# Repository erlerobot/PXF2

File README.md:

#The PixHawk Fire Cape 2.0 (PXF 2.0)

The PixHawk Fire Cape 2.0 (PXF 2.0) is an open hardware multi-platform shield for making drones using the APM autopilot supported by the Dronecode Foundation. This board is the evolution of the PXF, a project initiated by Philip Rowse to create an open hardware daughter board for Linux-based autopilots.

The shield is compatible with the following boards:

- BeagleBone Black
- Raspberry Pi
- Raspberry Pi 2
- Banana Pi
- Orange Pi
- Odroid-C1
- Odroid-C1+

(Note: not all these boards have been tested experimentally but the shield offers compatibility with the corresponding headers)

### Acquire the board
THIS SHIELD IS NOT SOLD INDIVIDUALLY. COMMERCIAL SOLUTIONS BASED ON THE PIXHAWK FIRE CAPE 2.0 ARE LISTED BELOW:
- [Erle-Brain 2.0](http://erlerobotics.com/blog/product/erle-brain-v2/)

If you'd like to be listed here contact victor@erlerobotics.com.

### Acknowledgements
This work has been enabled by Philip Rowse, Andrew Tridgell, Siddarth Purohit and all the contributors and supporters of the BeaglePilot, APM, and PX4 projects. Special mention to the DIYDrones community.

### License
GPLv3

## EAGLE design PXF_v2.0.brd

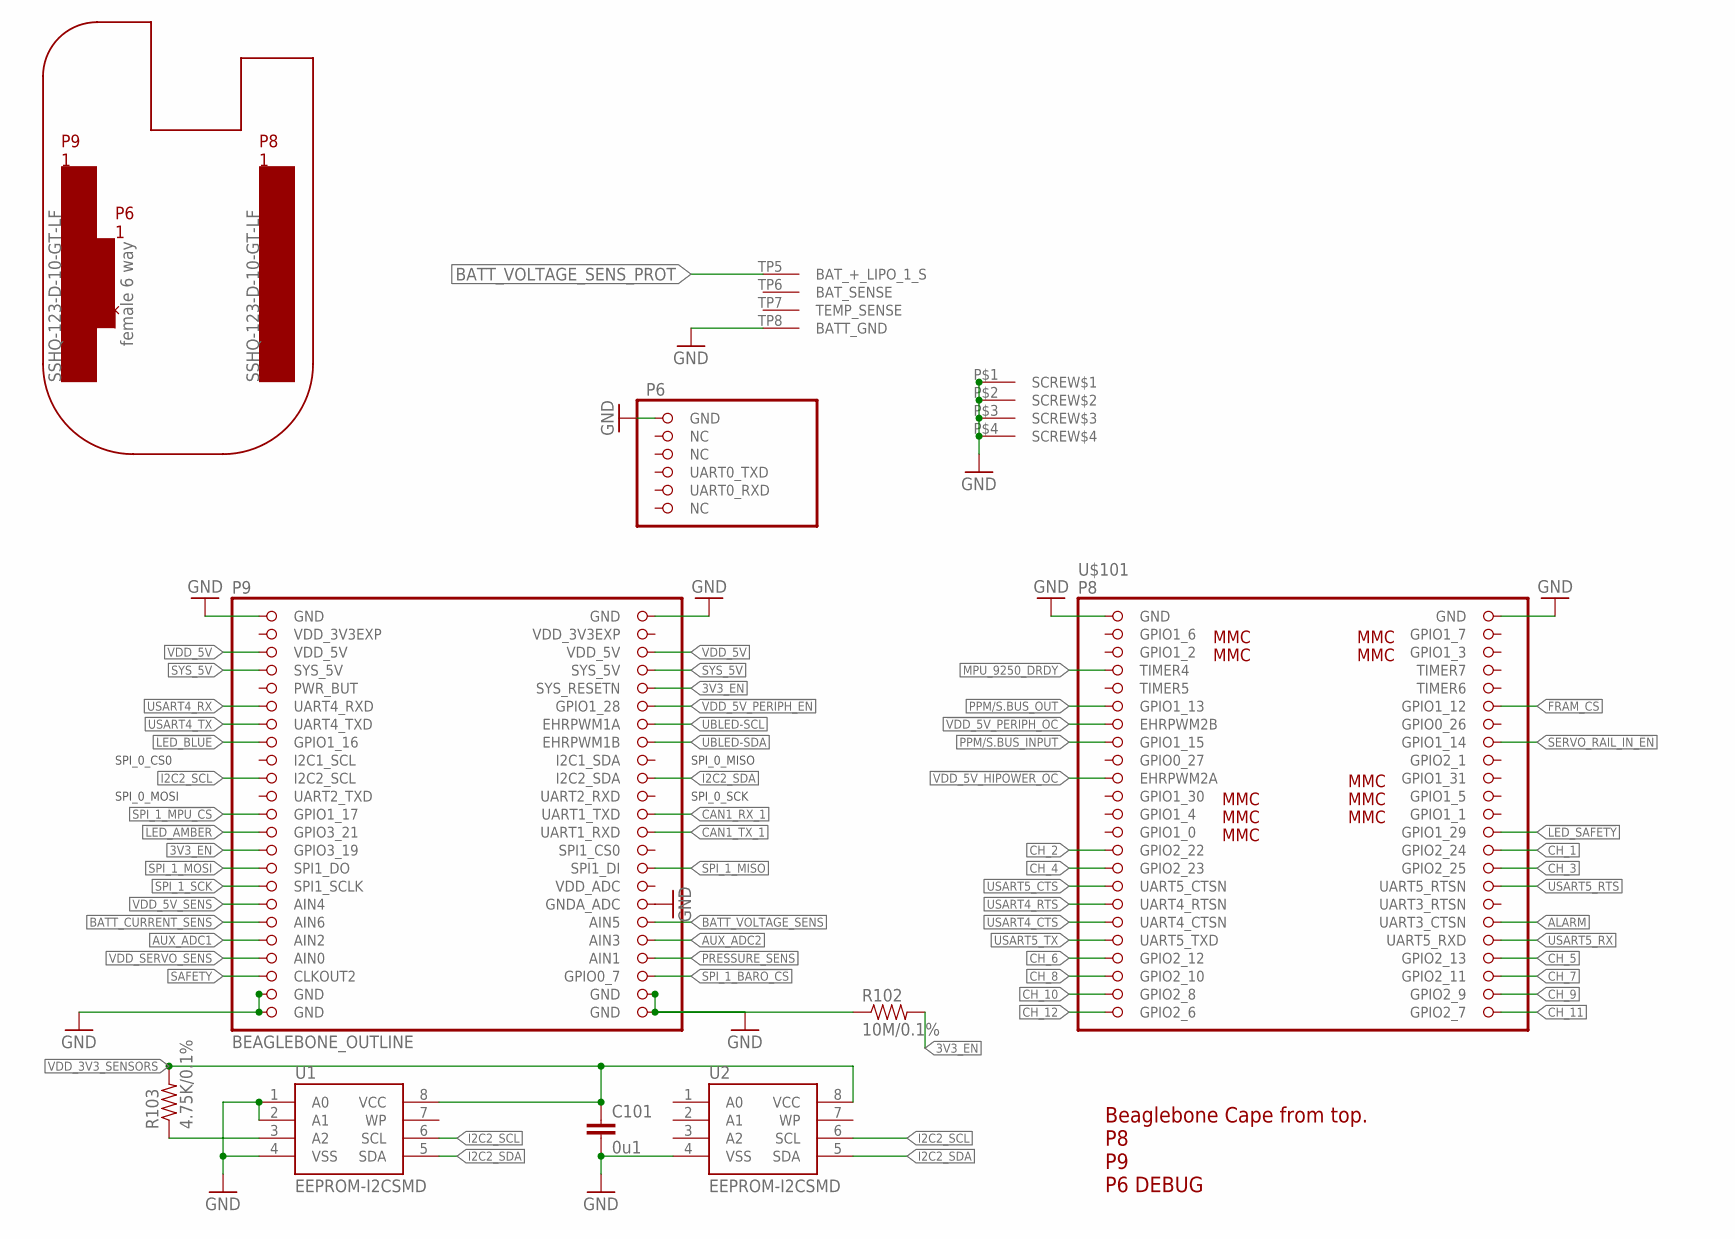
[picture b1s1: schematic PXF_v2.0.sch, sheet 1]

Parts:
C101: 0u1; 0402-CAP; PARTNO CC0402ZRY5V7BB104
R102: 10M/0.1%; 0402-RES; PARTNO RC0402FR-0710ML
R103: 4.75K/0.1%; 0402-RES; PARTNO RC0402FR-074K75L
U1: EEPROM-I2CSMD; SO08; PARTNO AT24CS32-SSHM
U2: EEPROM-I2CSMD; SO08; PARTNO ATSHA204-SH-DA-TTR-ND
U$101: BEAGLEBONE_OUTLINE; BEAGLEBONE_SHIELD

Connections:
3V3_EN: R102.P$2 (2), U$101.56 (SYS_RESETN), U$101.73 (GPIO3_19); also elsewhere on the board
!FRAM_CS: U$101.12 (GPIO1_12); also elsewhere on the board
!LED_AMBER: U$101.71 (GPIO3_21); also elsewhere on the board
!LED_BLUE: U$101.61 (GPIO1_16); also elsewhere on the board
!LED_SAFETY: U$101.26 (GPIO1_29); also elsewhere on the board
!VDD_5V_HIPOWER_OC: U$101.19 (EHRPWM2A); also elsewhere on the board
!VDD_5V_PERIPH_EN: U$101.58 (GPIO1_28); also elsewhere on the board
!VDD_5V_PERIPH_OC: U$101.13 (EHRPWM2B); also elsewhere on the board
ALARM: U$101.36 (UART3_CTSN); also elsewhere on the board
AUX_ADC1: U$101.83 (AIN2); also elsewhere on the board
AUX_ADC2: U$101.84 (AIN3); also elsewhere on the board
BATT_CURRENT_SENS: U$101.81 (AIN6); also elsewhere on the board
BATT_VOLTAGE_SENS: U$101.82 (AIN5); also elsewhere on the board
BATT_VOLTAGE_SENS_PROT: U$101.TP5 (BAT_+_LIPO_1_S); also elsewhere on the board
CAN1_RX_1: U$101.70 (UART1_TXD); also elsewhere on the board
CAN1_TX_1: U$101.72 (UART1_RXD); also elsewhere on the board
CH_1: U$101.28 (GPIO2_24); also elsewhere on the board
CH_2: U$101.27 (GPIO2_22); also elsewhere on the board
CH_3: U$101.30 (GPIO2_25); also elsewhere on the board
CH_4: U$101.29 (GPIO2_23); also elsewhere on the board
CH_5: U$101.40 (GPIO2_13); also elsewhere on the board
CH_6: U$101.39 (GPIO2_12); also elsewhere on the board
CH_7: U$101.42 (GPIO2_11); also elsewhere on the board
CH_8: U$101.41 (GPIO2_10); also elsewhere on the board
CH_9: U$101.44 (GPIO2_9); also elsewhere on the board
CH_10: U$101.43 (GPIO2_8); also elsewhere on the board
CH_11: U$101.46 (GPIO2_7); also elsewhere on the board
CH_12: U$101.45 (GPIO2_6); also elsewhere on the board
GND: C101.P$2 (2), R102.P$1 (1), U1.1 (A0), U1.2 (A1), U1.4 (VSS), U2.4 (VSS), U$101.1 (GND), U$101.2 (GND), U$101.47 (GND), U$101.48 (GND), U$101.80 (GNDA_ADC), U$101.89 (GND), U$101.90 (GND), U$101.91 (GND), U$101.92 (GND), U$101.93 (GND), U$101.P$1 (SCREW$1), U$101.P$2 (SCREW$2), U$101.P$3 (SCREW$3), U$101.P$4 (SCREW$4), U$101.TP8 (BATT_GND); also elsewhere on the board
I2C2_SCL: U1.6 (SCL), U2.6 (SCL), U$101.65 (I2C2_SCL); also elsewhere on the board
I2C2_SDA: U1.5 (SDA), U2.5 (SDA), U$101.66 (I2C2_SDA); also elsewhere on the board
MPU_9250_DRDY: U$101.7 (TIMER4); also elsewhere on the board
unnamed: R103.P$1 (1), U1.3 (A2)
PPM/S.BUS_INPUT: U$101.15 (GPIO1_15); also elsewhere on the board
PPM/S.BUS_OUT: U$101.11 (GPIO1_13); also elsewhere on the board
PRESSURE_SENS: U$101.86 (AIN1); also elsewhere on the board
SAFETY: U$101.87 (CLKOUT2); also elsewhere on the board
SERVO_RAIL_IN_!EN: U$101.16 (GPIO1_14)
SPI_1_!BARO_CS: U$101.88 (GPIO0_7); also elsewhere on the board
SPI_1_!MPU_CS: U$101.69 (GPIO1_17); also elsewhere on the board
SPI_1_MISO: U$101.76 (SPI1_DI); also elsewhere on the board
SPI_1_MOSI: U$101.75 (SPI1_DO); also elsewhere on the board
SPI_1_SCK: U$101.77 (SPI1_SCLK); also elsewhere on the board
SYS_5V: U$101.53 (SYS_5V), U$101.54 (SYS_5V); also elsewhere on the board
UBLED-SCL: U$101.60 (EHRPWM1A); also elsewhere on the board
UBLED-SDA: U$101.62 (EHRPWM1B); also elsewhere on the board
USART4_CTS: U$101.35 (UART4_CTSN); also elsewhere on the board
USART4_RTS: U$101.33 (UART4_RTSN); also elsewhere on the board
USART4_RX: U$101.57 (UART4_RXD); also elsewhere on the board
USART4_TX: U$101.59 (UART4_TXD); also elsewhere on the board
USART5_CTS: U$101.31 (UART5_CTSN); also elsewhere on the board
USART5_RTS: U$101.32 (UART5_RTSN); also elsewhere on the board
USART5_RX: U$101.38 (UART5_RXD); also elsewhere on the board
USART5_TX: U$101.37 (UART5_TXD); also elsewhere on the board
VDD_3V3EXP: U$101.49 (VDD_3V3EXP), U$101.50 (VDD_3V3EXP)
VDD_3V3_SENSORS: C101.P$1 (1), R103.P$2 (2), U1.8 (VCC), U2.8 (VCC); also elsewhere on the board
VDD_5V: U$101.51 (VDD_5V), U$101.52 (VDD_5V); also elsewhere on the board
VDD_5V_SENS: U$101.79 (AIN4); also elsewhere on the board
VDD_SERVO_SENS: U$101.85 (AIN0); also elsewhere on the board

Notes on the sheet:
Beaglebone Cape from top. P8 P9 P6 DEBUG
SPI_0_CS0
SPI_0_MOSI
SPI_0_MISO
SPI_0_SCK

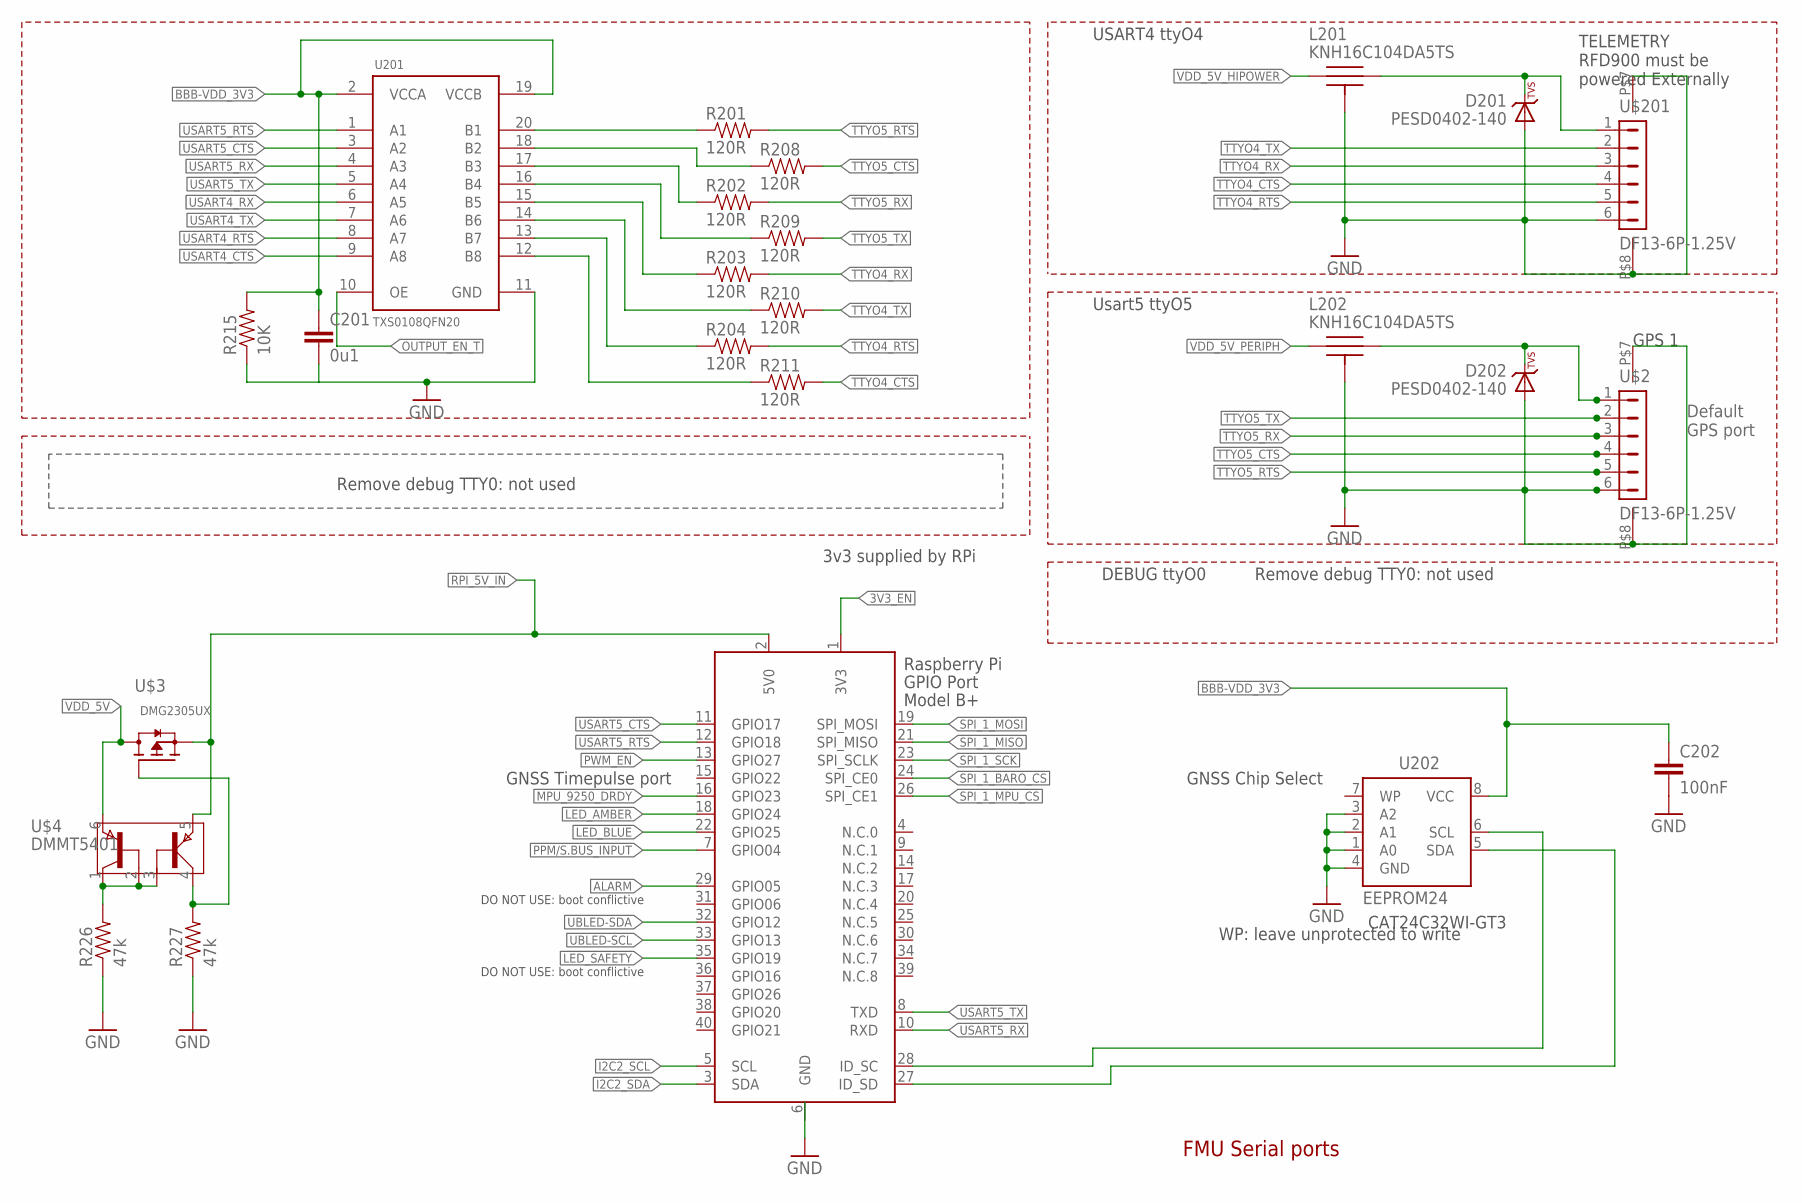
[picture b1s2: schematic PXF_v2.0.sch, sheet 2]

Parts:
C201: 0u1; 0402-CAP; PARTNO CC0402ZRY5V7BB104
C202: 100nF; 0402-CAP; PARTNO CC0402ZRY5V7BB104
D201, D202: PESD0402-140; 0402-TVS; PARTNO PESD0402-140
L201, L202: KNH16C104DA5TS; KYOCERA-KNH16-DA; PARTNO KNH16C104DA5TS
R201, R202, R203, R204, R208, R209, R210, R211: 120R; 0402-RES; PARTNO RC0402FR-07120RL
R215: 10K; 0402-RES; PARTNO ERA-2AEB103X
R226, R227: 47k; 0402-RES; PARTNO RC0402FR-07120RL
U201: TXS0108QFN20; QFN20-RGY; PARTNO TXS0108ERGYR
U202: EEPROM24; SOIC8
U$2, U$201: DF13-6P-1.25V; DF13C-6P-1.25V; PARTNO DF13C-6P-1.25V(20)
U$3: P-MOSFET; SOT23
U$4: DMMT5401; SOT26
X2: RASPI_BOARD_B+_F; RASPI_BOARD_B+_FULL

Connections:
3V3_EN: X2.1 (3V3); also elsewhere on the board
!LED_AMBER: X2.18 (GPIO24); also elsewhere on the board
!LED_BLUE: X2.22 (GPIO25); also elsewhere on the board
!LED_SAFETY: X2.35 (GPIO19); also elsewhere on the board
ALARM: X2.29 (GPIO05); also elsewhere on the board
BBB-VDD_3V3: C201.P$1 (1), C202.P$1 (1), R215.P$2 (2), U201.2 (VCCA), U201.19 (VCCB), U202.8 (VCC); also elsewhere on the board
GND: C201.P$2 (2), C202.P$2 (2), D201.A, D202.A, L201.P$3, L201.P$4, L201.P$5, L202.P$3, L202.P$4, L202.P$5, R215.P$1 (1), R226.P$1 (1), R227.P$1 (1), U201.11 (GND), U202.1 (A0), U202.2 (A1), U202.3 (A2), U202.4 (GND), U$2.6, U$2.P$7, U$2.P$8, U$201.6, U$201.P$7, U$201.P$8, X2.6 (GND); also elsewhere on the board
I2C2_SCL: X2.5 (SCL); also elsewhere on the board
I2C2_SDA: X2.3 (SDA); also elsewhere on the board
MPU_9250_DRDY: X2.16 (GPIO23); also elsewhere on the board
unnamed: U202.6 (SCL), X2.28 (ID_SC)
unnamed: U202.5 (SDA), X2.27 (ID_SD)
unnamed: D201.C, L201.P$2, U$201.1
unnamed: R226.P$2 (2), U$4.1, U$4.2, U$4.3
unnamed: R227.P$2 (2), U$3.G, U$4.4
unnamed: R208.P$1 (1), U201.18 (B2)
unnamed: R201.P$1 (1), U201.20 (B1)
unnamed: R202.P$1 (1), U201.17 (B3)
unnamed: R209.P$1 (1), U201.16 (B4)
unnamed: R203.P$1 (1), U201.15 (B5)
unnamed: R210.P$1 (1), U201.14 (B6)
unnamed: R204.P$1 (1), U201.13 (B7)
unnamed: R211.P$1 (1), U201.12 (B8)
unnamed: D202.C, L202.P$2, U$2.1
OUTPUT_EN_T: U201.10 (OE); also elsewhere on the board
PPM/S.BUS_INPUT: X2.7 (GPIO04); also elsewhere on the board
PWM_EN: X2.13 (GPIO27); also elsewhere on the board
RPI_5V_IN: U$3.S, U$4.5, X2.2 (5V0); also elsewhere on the board
SPI_1_!BARO_CS: X2.24 (SPI_CE0); also elsewhere on the board
SPI_1_!MPU_CS: X2.26 (SPI_CE1); also elsewhere on the board
SPI_1_MISO: X2.21 (SPI_MISO); also elsewhere on the board
SPI_1_MOSI: X2.19 (SPI_MOSI); also elsewhere on the board
SPI_1_SCK: X2.23 (SPI_SCLK); also elsewhere on the board
TTYO4_CTS: R211.P$2 (2), U$201.4
TTYO4_RTS: R204.P$2 (2), U$201.5
TTYO4_RX: R203.P$2 (2), U$201.3; also elsewhere on the board
TTYO4_TX: R210.P$2 (2), U$201.2; also elsewhere on the board
TTYO5_CTS: R208.P$2 (2), U$2.4
TTYO5_RTS: R201.P$2 (2), U$2.5
TTYO5_RX: R202.P$2 (2), U$2.3; also elsewhere on the board
TTYO5_TX: R209.P$2 (2), U$2.2; also elsewhere on the board
UBLED-SCL: X2.33 (GPIO13); also elsewhere on the board
UBLED-SDA: X2.32 (GPIO12); also elsewhere on the board
USART4_CTS: U201.9 (A8); also elsewhere on the board
USART4_RTS: U201.8 (A7); also elsewhere on the board
USART4_RX: U201.6 (A5); also elsewhere on the board
USART4_TX: U201.7 (A6); also elsewhere on the board
USART5_CTS: U201.3 (A2), X2.11 (GPIO17); also elsewhere on the board
USART5_RTS: U201.1 (A1), X2.12 (GPIO18); also elsewhere on the board
USART5_RX: U201.4 (A3), X2.10 (RXD); also elsewhere on the board
USART5_TX: U201.5 (A4), X2.8 (TXD); also elsewhere on the board
VDD_5V: U$3.D, U$4.6; also elsewhere on the board
VDD_5V_HIPOWER: L201.P$1; also elsewhere on the board
VDD_5V_PERIPH: L202.P$1; also elsewhere on the board

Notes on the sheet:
FMU Serial ports
Usart5 ttyO5
USART4 ttyO4
DEBUG ttyO0
Default GPS port
TELEMETRY RFD900 must be powered Externally
GPS 1
Remove debug TTY0: not used
CAT24C32WI-GT3
3v3 supplied by RPi
GNSS Timepulse port
GNSS Chip Select
DO NOT USE: boot conflictive
WP: leave unprotected to write

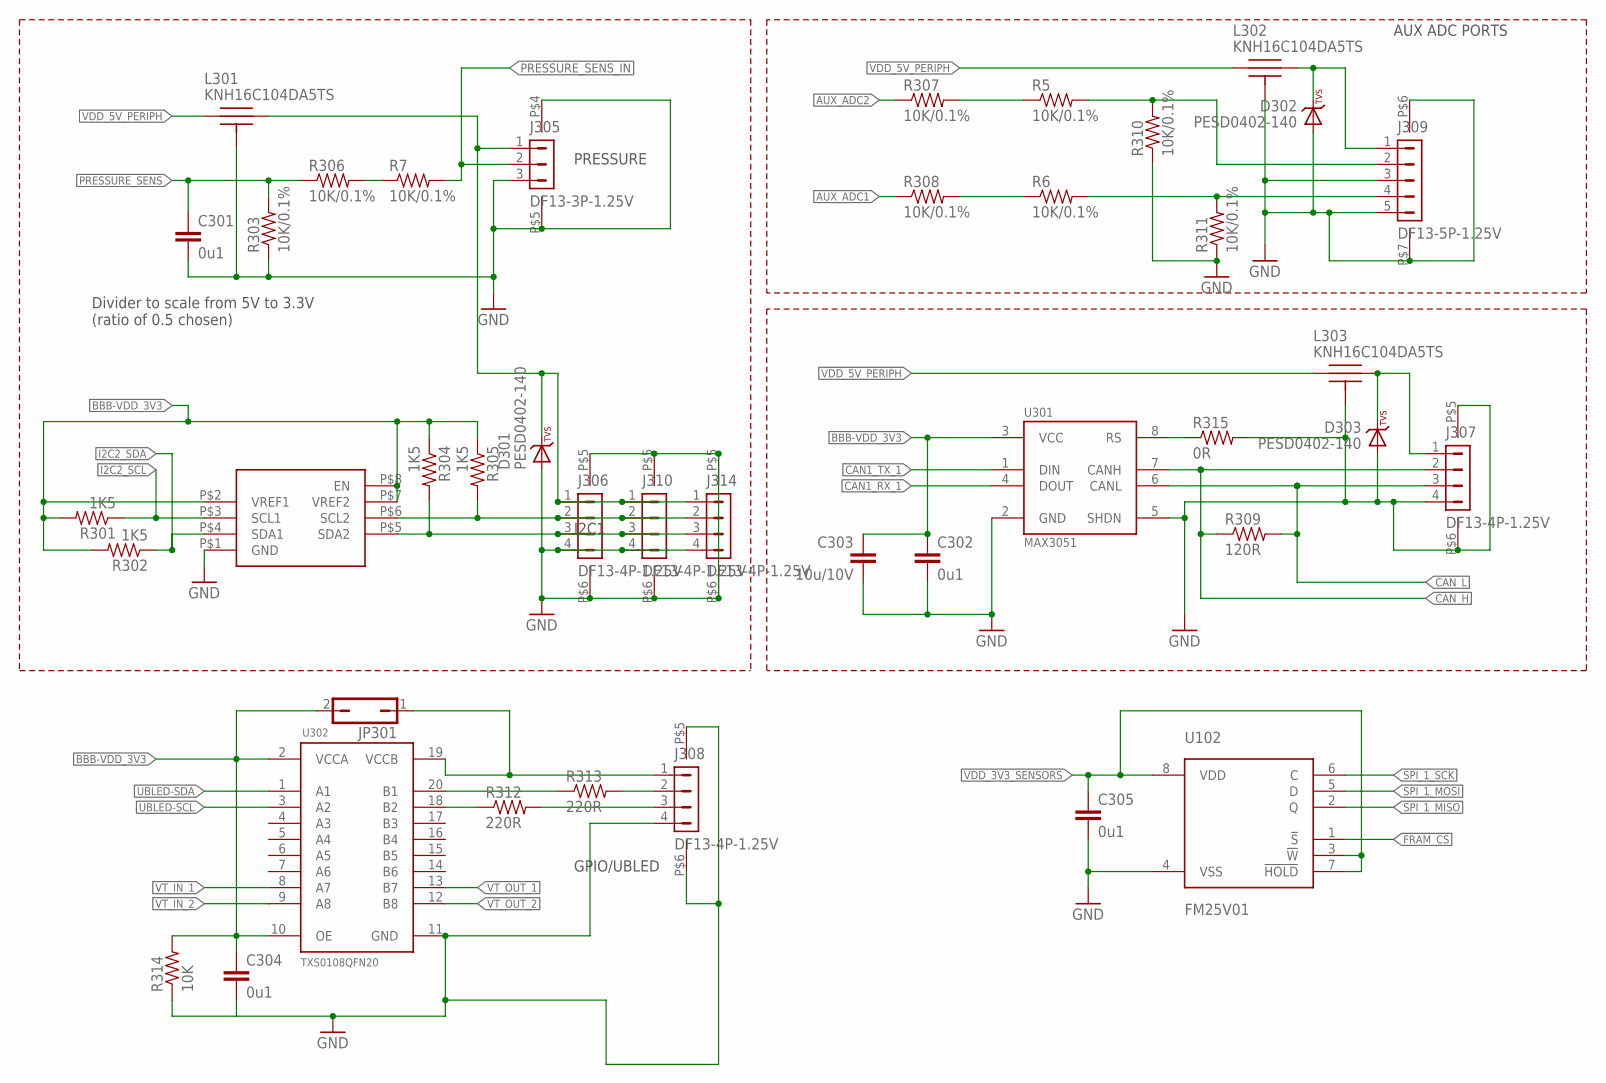
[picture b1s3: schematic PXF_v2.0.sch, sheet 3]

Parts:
C301, C302, C304, C305: 0u1; 0402-CAP; PARTNO CC0402ZRY5V7BB104
C303: 10u/10V; 0805-CAP; PARTNO CC0805ZKY5V6BB106
D301, D302, D303: PESD0402-140; 0402-TVS; PARTNO PESD0402-140
J305: DF13-3P-1.25V; DF13C-3P-1.25V; PARTNO DF13C-3P-1.25V(20)
J306, J307, J308, J310, J314: DF13-4P-1.25V; DF13C-4P-1.25V; PARTNO DF13C-4P-1.25V(20)
J309: DF13-5P-1.25V; DF13C-5P-1.25V; PARTNO DF13C-5P-1.25V(20)
JP301: JP1Q; JP1; PARTNO 1-87215-0
L301, L302, L303: KNH16C104DA5TS; KYOCERA-KNH16-DA; PARTNO KNH16C104DA5TS
R5, R6, R7, R303, R306, R307, R308, R310, R311: 10K/0.1%; 0402-RES; PARTNO ERA-2AEB103X
R301, R302, R304, R305: 1K5; 0402-RES; PARTNO RC0402FR-071K5L
R309: 120R; 0402-RES; PARTNO RC0402FR-07120RL
R312, R313: 220R; 0402-RES; PARTNO RC0402FR-07220RL
R314: 10K; 0402-RES; PARTNO ERA-2AEB103X
R315: 0R; 0402-RES; PARTNO RC0402FR-070RL
U102: FM25V01; SO08; PARTNO FM25V01-G
U301: MAX3051; SOT23-8; PARTNO MAX3051EKA
U302: TXS0108QFN20; QFN20-RGY; PARTNO TXS0108ERGYR
U304: PCA9603; DCT

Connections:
!FRAM_CS: U102.1 (!S); also elsewhere on the board
AUX_ADC1: R308.P$1 (1); also elsewhere on the board
AUX_ADC2: R307.P$1 (1); also elsewhere on the board
BBB-VDD_3V3: C302.P$1 (1), C303.P$1 (1), C304.P$1 (1), JP301.2, R301.P$2 (2), R302.P$2 (2), R304.P$1 (1), R305.P$1 (1), R314.P$2 (2), U301.3 (VCC), U302.2 (VCCA), U302.10 (OE), U304.P$2 (VREF1), U304.P$7 (VREF2), U304.P$8 (EN); also elsewhere on the board
CAN1_RX_1: U301.4 (DOUT); also elsewhere on the board
CAN1_TX_1: U301.1 (DIN); also elsewhere on the board
CAN_H: J307.2, R309.P$1 (1), U301.7 (CANH); also elsewhere on the board
CAN_L: J307.3, R309.P$2 (2), U301.6 (CANL); also elsewhere on the board
FMU_AUX_ADC1_PROT: J309.4, R6.P$2 (2), R311.P$2 (2)
FMU_AUX_ADC2_PROT: J309.2, R5.P$2 (2), R310.P$2 (2)
GND: C301.P$2 (2), C302.P$2 (2), C303.P$2 (2), C304.P$2 (2), C305.P$2 (2), D301.A, D302.A, D303.A, J305.3, J305.P$4, J305.P$5, J306.4, J306.P$5, J306.P$6, J307.4, J307.P$5, J307.P$6, J308.4, J308.P$5, J308.P$6, J309.3, J309.5, J309.P$6, J309.P$7, J310.4, J310.P$5, J310.P$6, J314.4, J314.P$5, J314.P$6, L301.P$3, L301.P$4, L301.P$5, L302.P$3, L302.P$4, L302.P$5, L303.P$3, L303.P$4, L303.P$5, R303.P$1 (1), R310.P$1 (1), R311.P$1 (1), R314.P$1 (1), R315.P$2 (2), U102.4 (VSS), U301.2 (GND), U301.5 (SHDN), U302.11 (GND), U304.P$1 (GND); also elsewhere on the board
I2C2_SCL: R301.P$1 (1), U304.P$3 (SCL1); also elsewhere on the board
I2C2_SDA: R302.P$1 (1), U304.P$4 (SDA1); also elsewhere on the board
unnamed: R313.P$1 (1), U302.20 (B1)
unnamed: J306.2, J310.2, J314.2, R305.P$2 (2), U304.P$6 (SCL2)
unnamed: J306.3, J310.3, J314.3, R304.P$2 (2), U304.P$5 (SDA2)
unnamed: R312.P$1 (1), U302.18 (B2)
unnamed: D301.C, J305.1, J306.1, J310.1, J314.1, L301.P$2
unnamed: J308.3, R312.P$2 (2)
unnamed: J308.2, R313.P$2 (2)
unnamed: J308.1, JP301.1, U302.19 (VCCB)
unnamed: D303.C, J307.1, L303.P$2
unnamed: R315.P$1 (1), U301.8 (RS)
unnamed: R5.P$1 (1), R307.P$2 (2)
unnamed: R6.P$1 (1), R308.P$2 (2)
unnamed: R7.P$1 (1), R306.P$2 (2)
unnamed: D302.C, J309.1, L302.P$2
PRESSURE_SENS: C301.P$1 (1), R303.P$2 (2), R306.P$1 (1); also elsewhere on the board
PRESSURE_SENS_IN: J305.2, R7.P$2 (2); also elsewhere on the board
SPI_1_MISO: U102.2 (Q); also elsewhere on the board
SPI_1_MOSI: U102.5 (D); also elsewhere on the board
SPI_1_SCK: U102.6 (C); also elsewhere on the board
UBLED-SCL: U302.3 (A2); also elsewhere on the board
UBLED-SDA: U302.1 (A1); also elsewhere on the board
VDD_3V3_SENSORS: C305.P$1 (1), U102.3 (!W), U102.7 (!HOLD), U102.8 (VDD); also elsewhere on the board
VDD_5V_PERIPH: L301.P$1, L302.P$1, L303.P$1; also elsewhere on the board
VT_IN_1: U302.8 (A7); also elsewhere on the board
VT_IN_2: U302.9 (A8); also elsewhere on the board
VT_OUT_1: U302.13 (B7); also elsewhere on the board
VT_OUT_2: U302.12 (B8); also elsewhere on the board

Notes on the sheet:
PRESSURE
I2C1
AUX ADC PORTS
Divider to scale from 5V to 3.3V (ratio of 0.5 chosen)
GPIO/UBLED

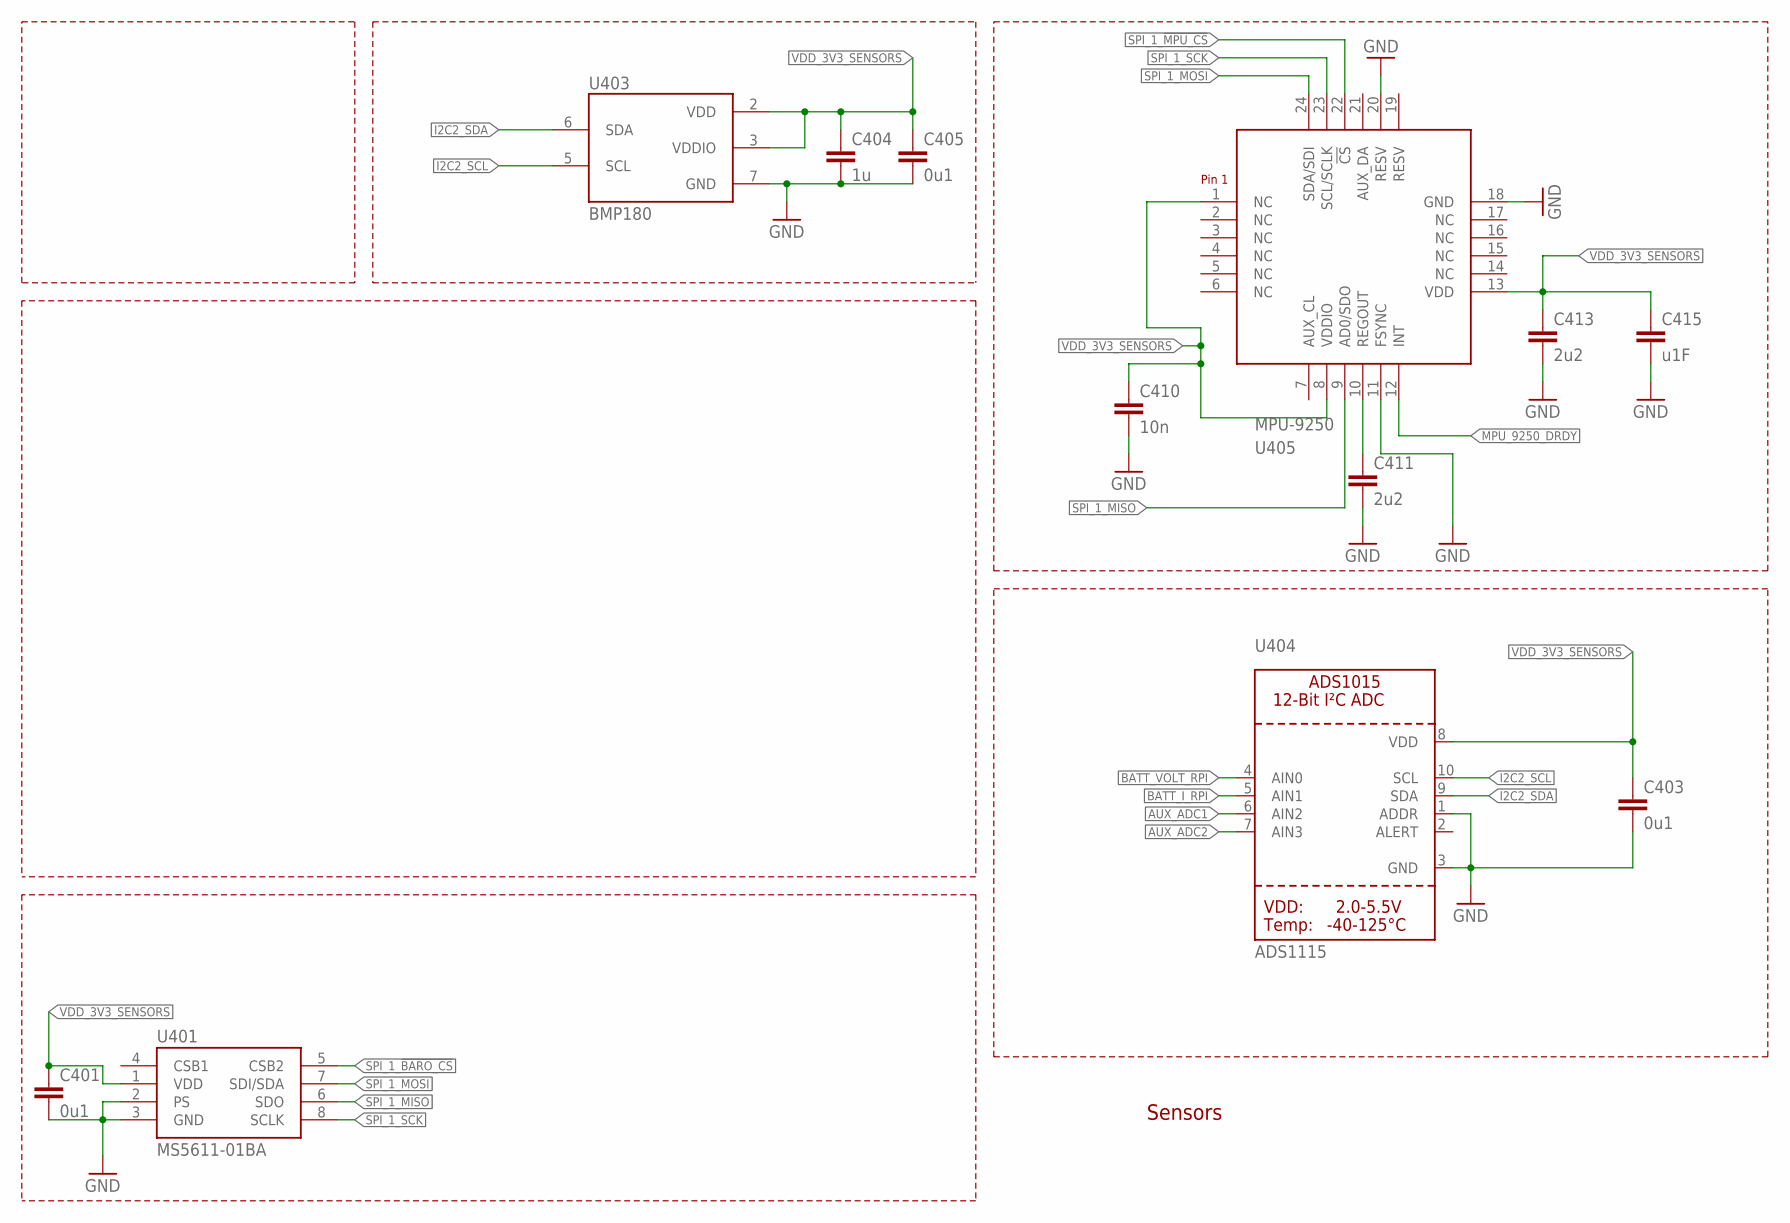
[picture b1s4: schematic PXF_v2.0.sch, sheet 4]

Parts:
C401, C403, C405: 0u1; 0402-CAP; PARTNO CC0402ZRY5V7BB104
C404: 1u; 0402-CAP; PARTNO CC0402ZRY5V7BB104
C410: 10n; 0603-CAP; PARTNO C0603C103J5RAC7411
C411: 2u2; 0603-CAP; PARTNO C1608X6S1C225K080AC
C413: 2u2; 0603-CAP
C415: u1F; 0402-CAP; PARTNO CC0402ZRY5V7BB104
U401: MS5611-01BA; PARTNO MS5611-01BA
U403: BMP180
U404: ADS1115; MSOP10
U405: MPU-9250; MPU-6500; PARTNO MPU-9250

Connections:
AUX_ADC1: U404.6 (AIN2); also elsewhere on the board
AUX_ADC2: U404.7 (AIN3); also elsewhere on the board
BATT_I_RPI: U404.5 (AIN1); also elsewhere on the board
BATT_VOLT_RPI: U404.4 (AIN0); also elsewhere on the board
GND: C401.P$2 (2), C403.P$2 (2), C404.P$2 (2), C405.P$2 (2), C410.P$2 (2), C411.P$2 (2), C413.P$2 (2), C415.P$2 (2), U401.2 (PS), U401.3 (GND), U403.7 (GND), U404.1 (ADDR), U404.3 (GND), U405.11 (FSYNC), U405.18 (GND), U405.20 (RESV); also elsewhere on the board
I2C2_SCL: U403.5 (SCL), U404.10 (SCL); also elsewhere on the board
I2C2_SDA: U403.6 (SDA), U404.9 (SDA); also elsewhere on the board
MPU_9250_DRDY: U405.12 (INT); also elsewhere on the board
unnamed: C411.P$1 (1), U405.10 (REGOUT)
SPI_1_!BARO_CS: U401.5 (CSB2); also elsewhere on the board
SPI_1_!MPU_CS: U405.22 (!CS); also elsewhere on the board
SPI_1_MISO: U401.6 (SDO), U405.9 (AD0/SDO); also elsewhere on the board
SPI_1_MOSI: U401.7 (SDI/SDA), U405.24 (SDA/SDI); also elsewhere on the board
SPI_1_SCK: U401.8 (SCLK), U405.23 (SCL/SCLK); also elsewhere on the board
VDD_3V3_SENSORS: C401.P$1 (1), C403.P$1 (1), C404.P$1 (1), C405.P$1 (1), C410.P$1 (1), C413.P$1 (1), C415.P$1 (1), U401.1 (VDD), U403.2 (VDD), U403.3 (VDDIO), U404.8 (VDD), U405.1 (NC), U405.8 (VDDIO), U405.13 (VDD); also elsewhere on the board

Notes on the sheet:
Sensors

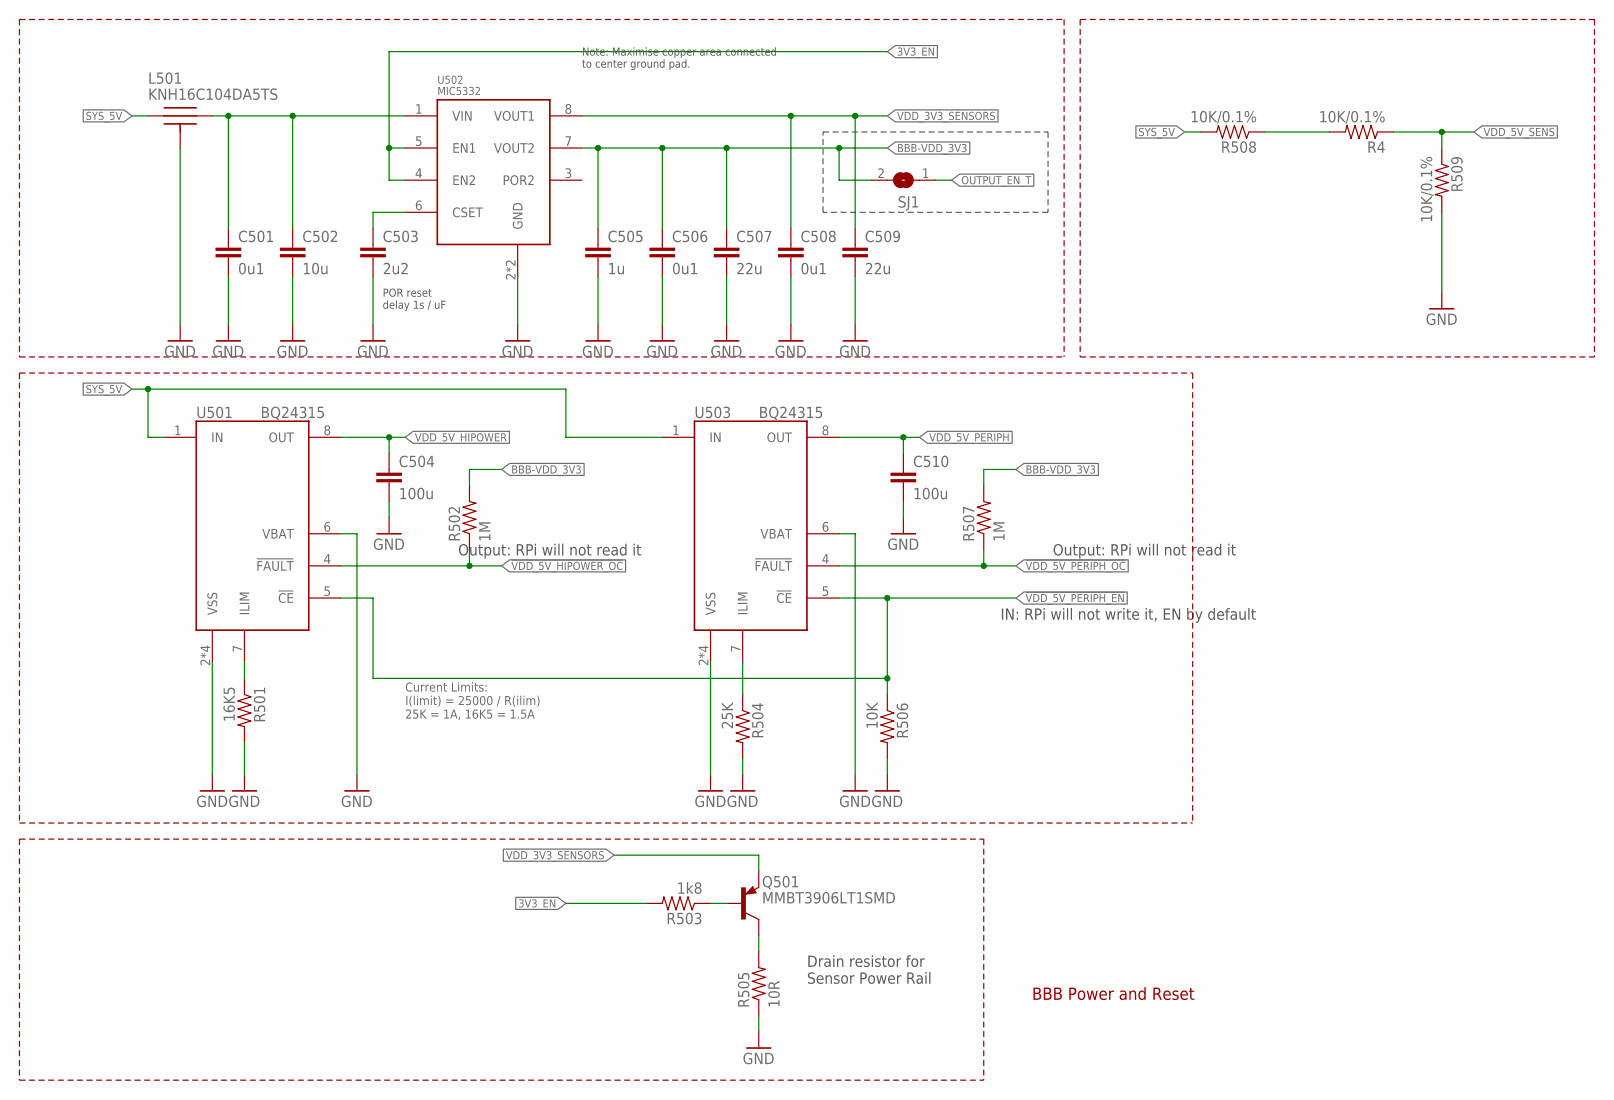
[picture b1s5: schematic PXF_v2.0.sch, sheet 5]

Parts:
C501, C506, C508: 0u1; 0402-CAP; PARTNO CC0402ZRY5V7BB104
C502: 10u; 0805-CAP; PARTNO C1608X7S0J106M080AC
C503: 2u2; 0603-CAP; PARTNO C1608X6S1C225K080AC
C504, C510: 100u; 1206-CAP; PARTNO C3216X5R1A107M160AC
C505: 1u; 0603-CAP; PARTNO CC0603ZRY5V7BB105
C507, C509: 22u; 0805-CAP; PARTNO CC0805MKX5R5BB226
L501: KNH16C104DA5TS; KYOCERA-KNH16-DA; PARTNO KNH16C104DA5TS
Q501: MMBT3906LT1SMD; SOT23-BEC; PARTNO MMBT3906LT1G
R4, R508, R509: 10K/0.1%; 0402-RES; PARTNO ERA-2AEB103X
R501: 16K5; 0402-RES; PARTNO RMCF0402FT16K5
R502, R507: 1M; 0402-RES; PARTNO MCR01MRTF1004
R503: 1k8; 0402-RES; PARTNO RC0402FR-071K8L
R504: 25K; 0402-RES; PARTNO RMCF0402FT25K5
R505: 10R; 0603-RES; PARTNO RC0402FR-0710RL
R506: 10K; 0402-RES; PARTNO ERA-2AEB103X
SJ1: SOLDERJUMPERCLOSED; SOLDERJUMPER_CLOSEDWIRE
U501, U503: BQ24315; QFN8-DSG; PARTNO BQ24315DSGR
U502: MIC5332; MLF-8-EPAD; PARTNO MIC5332-SSYMT

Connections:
3V3_EN: R503.P$2 (2), U502.4 (EN2), U502.5 (EN1); also elsewhere on the board
!VDD_5V_HIPOWER_OC: R502.P$1 (1), U501.4 (!FAULT); also elsewhere on the board
!VDD_5V_PERIPH_EN: R506.P$1 (1), U501.5 (!CE), U503.5 (!CE); also elsewhere on the board
!VDD_5V_PERIPH_OC: R507.P$1 (1), U503.4 (!FAULT); also elsewhere on the board
BBB-VDD_3V3: C505.P$1 (1), C506.P$1 (1), C507.P$1 (1), R502.P$2 (2), R507.P$2 (2), SJ1.2, U502.7 (VOUT2); also elsewhere on the board
FMU-VDD_5V5: C501.P$1 (1), C502.P$1 (1), L501.P$2, U502.1 (VIN)
GND: C501.P$2 (2), C502.P$2 (2), C503.P$2 (2), C504.P$2 (2), C505.P$2 (2), C506.P$2 (2), C507.P$2 (2), C508.P$2 (2), C509.P$2 (2), C510.P$2 (2), L501.P$3, L501.P$4, L501.P$5, R501.P$2 (2), R504.P$2 (2), R505.1, R506.P$2 (2), R509.P$2 (2), U501.2 (VSS), U501.6 (VBAT), U501.GND (VSS), U501.P$2 (VSS), U501.P$3 (VSS), U502.2 (GND), U502.GND, U503.2 (VSS), U503.6 (VBAT), U503.GND (VSS), U503.P$2 (VSS), U503.P$3 (VSS); also elsewhere on the board
unnamed: C503.P$1 (1), U502.6 (CSET)
unnamed: R504.P$1 (1), U503.7 (ILIM)
unnamed: R4.P$2 (2), R508.P$1 (1)
unnamed: Q501.C, R505.2
unnamed: Q501.B, R503.P$1 (1)
unnamed: R501.P$1 (1), U501.7 (ILIM)
OUTPUT_EN_T: SJ1.1; also elsewhere on the board
SYS_5V: L501.P$1, R508.P$2 (2), U501.1 (IN), U503.1 (IN); also elsewhere on the board
VDD_3V3_SENSORS: C508.P$1 (1), C509.P$1 (1), Q501.E, U502.8 (VOUT1); also elsewhere on the board
VDD_5V_HIPOWER: C504.P$1 (1), U501.8 (OUT); also elsewhere on the board
VDD_5V_PERIPH: C510.P$1 (1), U503.8 (OUT); also elsewhere on the board
VDD_5V_SENS: R4.P$1 (1), R509.P$1 (1); also elsewhere on the board

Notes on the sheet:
BBB Power and Reset
Note: Maximise copper area connected to center ground pad.
POR reset delay 1s / uF
Current Limits: I(limit) = 25000 / R(ilim) 25K = 1A, 16K5 = 1.5A
Drain resistor for Sensor Power Rail
Output: RPi will not read it
IN: RPi will not write it, EN by default

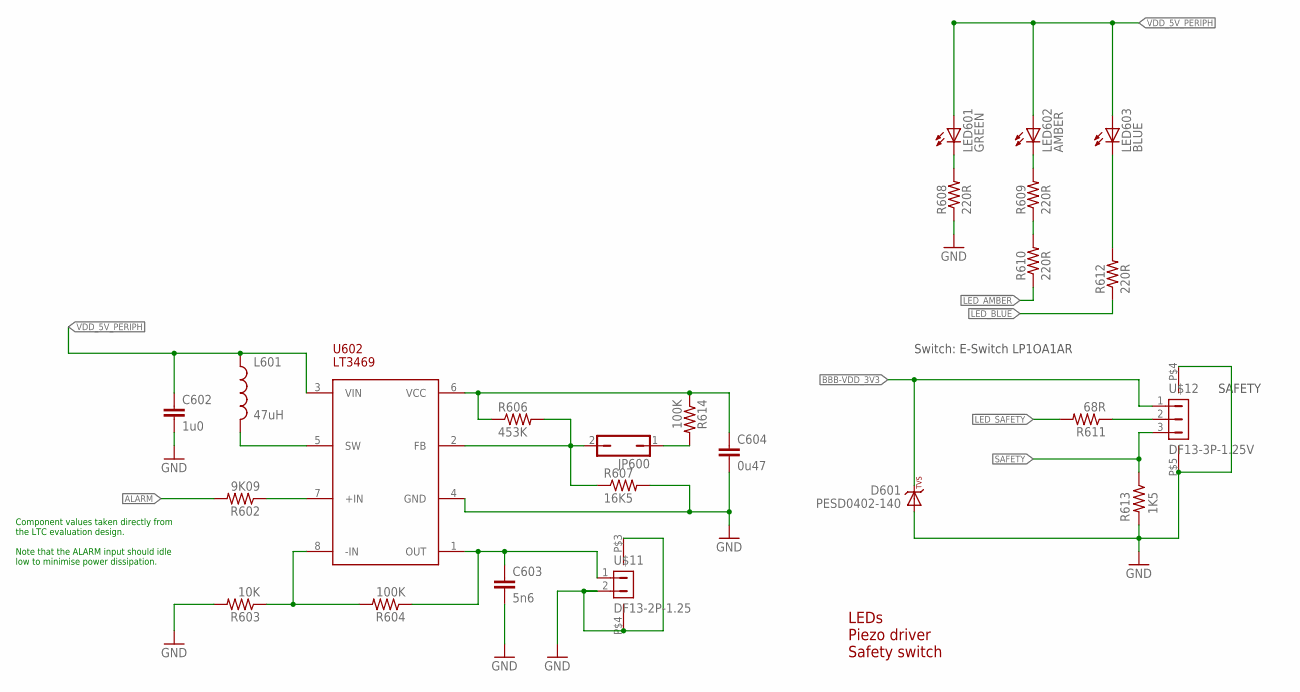
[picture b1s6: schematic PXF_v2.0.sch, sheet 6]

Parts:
C602: 1u0; 0603-CAP; PARTNO CC0603ZRY5V7BB105
C603: 5n6; 0402-CAP; PARTNO CC0402KRX7R7BB562
C604: 0u47; 0402-CAP; PARTNO C1005X5R1C474K050BC
D601: PESD0402-140; 0402-TVS; PARTNO PESD0402-140
JP600: JP1Q; JP1; PARTNO 1-87215-0
L601: 47uH; 0805-IND; PARTNO MLZ2012M470W
LED601: GREEN; 0603-LED; PARTNO APTD1608CGCK
LED602: AMBER; 0603-LED; PARTNO APTD1608SECK
LED603: BLUE; 0603-LED; PARTNO APTD1608QBC/D
R602: 9K09; 0402-RES; PARTNO RMCF0402FT9K09
R603: 10K; 0402-RES; PARTNO ERA-2AEB103X
R604, R614: 100K; 0402-RES; PARTNO RC0402FR-07100KL
R606: 453K; 0402-RES; PARTNO RMCF0402FT453K
R607: 16K5; 0402-RES; PARTNO RMCF0402FT16K5
R608, R609, R610, R612: 220R; 0402-RES; PARTNO RC0402FR-07220RL
R611: 68R; 0402-RES; PARTNO RC0402FR-0768RL
R613: 1K5; 0402-RES; PARTNO RC0402FR-071K5L
U602: LT3469; SOT23-8; PARTNO LT3469ETS8
U$11: DF13-2P-1.25; DF13C-2P-1.25V; PARTNO DF13C-2P-1.25V(20)
U$12: DF13-3P-1.25V; DF13C-3P-1.25V; PARTNO DF13C-3P-1.25V(20)

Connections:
!LED_AMBER: R610.P$1 (1); also elsewhere on the board
!LED_BLUE: R612.P$1 (1); also elsewhere on the board
!LED_SAFETY: R611.P$2 (2); also elsewhere on the board
ALARM: R602.P$2 (2); also elsewhere on the board
BBB-VDD_3V3: D601.C, U$12.1; also elsewhere on the board
GND: C602.P$2 (2), C603.P$2 (2), C604.P$2 (2), D601.A, R603.P$2 (2), R607.P$2 (2), R608.P$1 (1), R613.P$2 (2), U602.4 (GND), U$11.2, U$11.P$3, U$11.P$4, U$12.P$4, U$12.P$5; also elsewhere on the board
unnamed: LED603.C, R612.P$2 (2)
unnamed: JP600.2, R606.P$2 (2), R607.P$1 (1), U602.2 (FB)
unnamed: R603.P$1 (1), R604.P$2 (2), U602.8 (-IN)
unnamed: C603.P$1 (1), R604.P$1 (1), U602.1 (OUT), U$11.1
unnamed: R602.P$1 (1), U602.7 (+IN)
unnamed: LED601.C, R608.P$2 (2)
unnamed: L601.P$2 (2), U602.5 (SW)
unnamed: C604.P$1 (1), R606.P$1 (1), R614.P$1 (1), U602.6 (VCC)
unnamed: R609.P$1 (1), R610.P$2 (2)
unnamed: LED602.C, R609.P$2 (2)
unnamed: JP600.1, R614.P$2 (2)
unnamed: R611.P$1 (1), U$12.2
SAFETY: R613.P$1 (1), U$12.3; also elsewhere on the board
VDD_5V_PERIPH: C602.P$1 (1), L601.P$1 (1), LED601.A, LED602.A, LED603.A, U602.3 (VIN); also elsewhere on the board

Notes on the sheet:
LEDs Piezo driver Safety switch
Switch: E-Switch LP1OA1AR
SAFETY
Component values taken directly from the LTC evaluation design. Note that the ALARM input should idle low to minimise power dissipation.

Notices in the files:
parts and their libraries:
microbuilder: This work is placed in the public domain, and may be freely used for commercial and non-commercial work with the following conditions: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
SparkFun-Sensors: Licensing: CC v3.0 Share-Alike You are welcome to use this library for commercial purposes.
